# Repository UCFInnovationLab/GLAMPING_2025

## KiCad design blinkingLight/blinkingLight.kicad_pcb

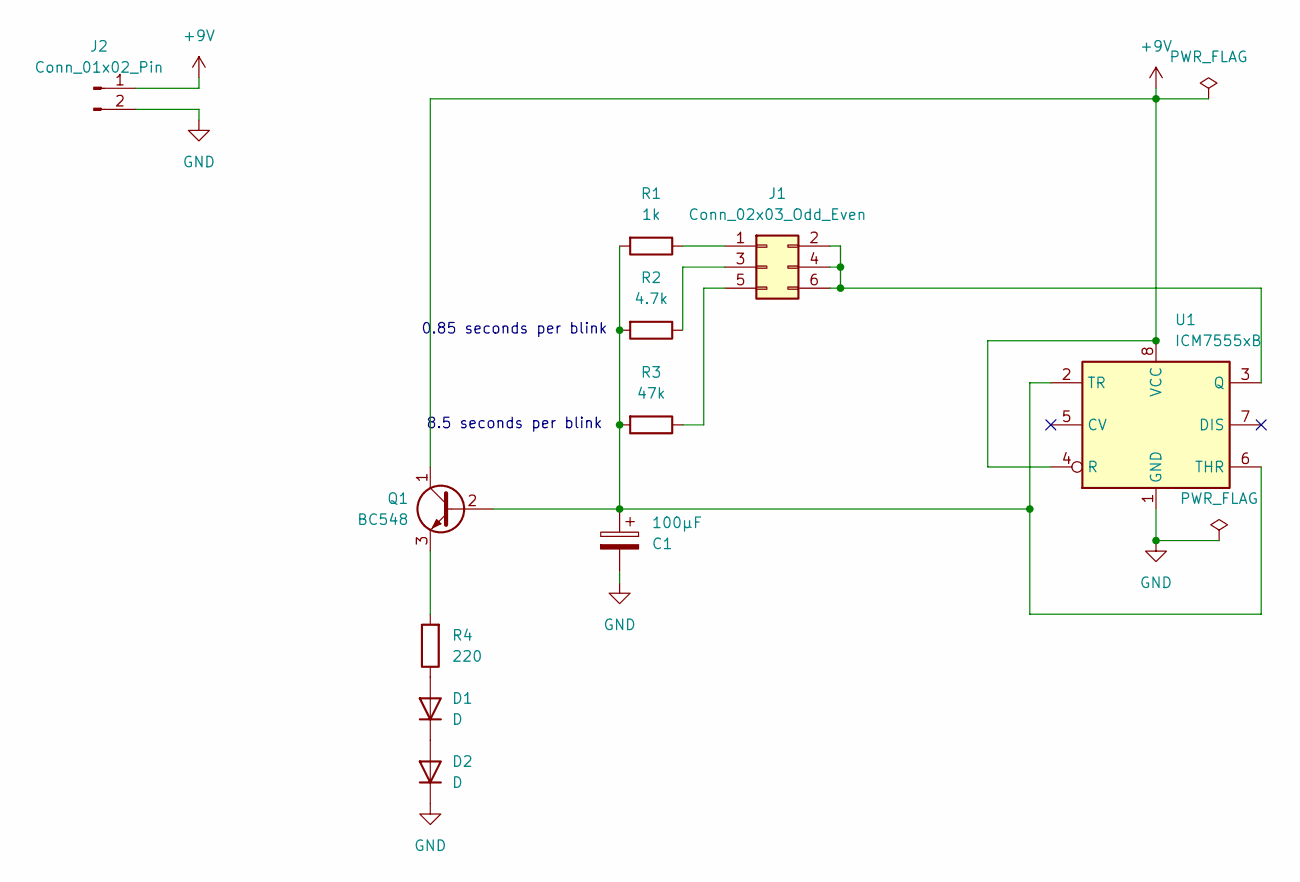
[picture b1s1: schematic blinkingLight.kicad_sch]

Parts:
C1: 100μF; CP_Radial_D5.0mm_P2.00mm
D1, D2: D; LED_D5.0mm
J1: Conn_02x03_Odd_Even; PinHeader_2x03_P2.54mm_Vertical
J2: Conn_01x02_Pin; TerminalBlock_Xinya_XY308-2.54-2P_1x02_P2.54mm_Horizontal
Q1: BC548; TO-92_Inline
R1: 1k; R_Axial_DIN0207_L6.3mm_D2.5mm_P10.16mm_Horizontal
R2: 4.7k; R_Axial_DIN0207_L6.3mm_D2.5mm_P10.16mm_Horizontal
R3: 47k; R_Axial_DIN0207_L6.3mm_D2.5mm_P10.16mm_Horizontal
R4: 220; R_Axial_DIN0207_L6.3mm_D2.5mm_P10.16mm_Horizontal
U1: ICM7555xB; DIP-8_W7.62mm

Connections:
+9V: J2.1, Q1.1 (C), U1.4 (R), U1.8 (VCC)
GND: C1.2, D2.1 (K), J2.2, U1.1 (GND)
unnamed: D1.2 (A), R4.1
unnamed: D1.1 (K), D2.2 (A)
unnamed: J1.1, R1.1
unnamed: J1.2, J1.4, J1.6, U1.3 (Q)
unnamed: J1.3, R2.1
unnamed: J1.5, R3.1
unnamed: C1.1, Q1.2 (B), R1.2, R2.2, R3.2, U1.2 (TR), U1.6 (THR)
unnamed: Q1.3 (E), R4.2

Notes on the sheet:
8.5 seconds per blink
0.85 seconds per blink

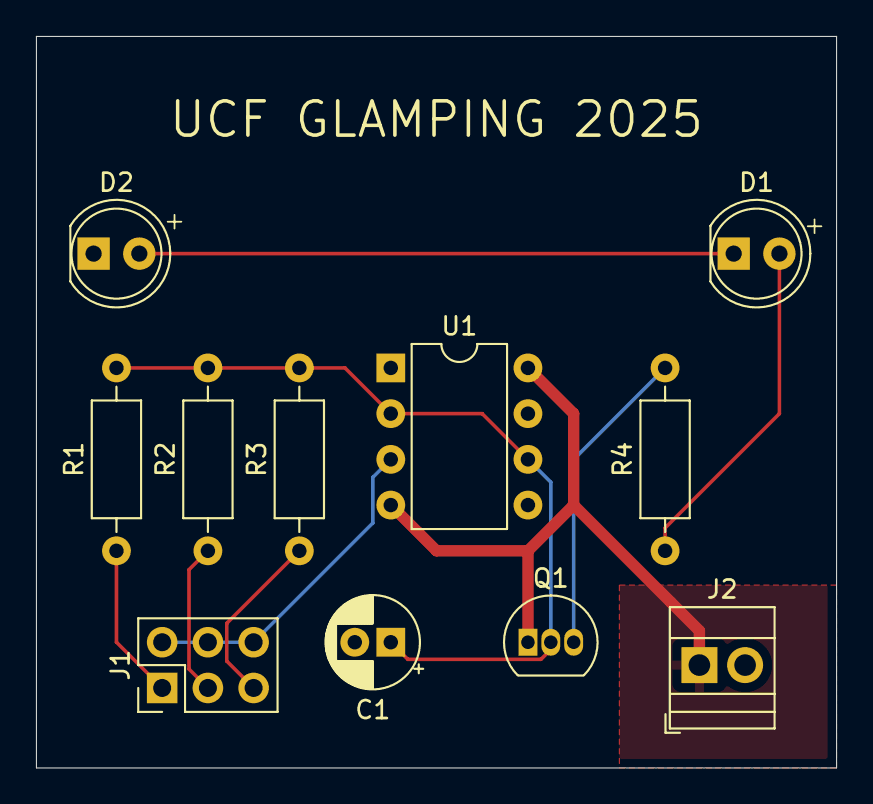
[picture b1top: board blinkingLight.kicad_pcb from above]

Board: 2 copper layers, 44.4 x 40.6 mm, 11 parts (0 on the bottom side), 10 nets.

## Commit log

2025-05-06 push
2025-05-07 fixed
2025-05-20 updated value
